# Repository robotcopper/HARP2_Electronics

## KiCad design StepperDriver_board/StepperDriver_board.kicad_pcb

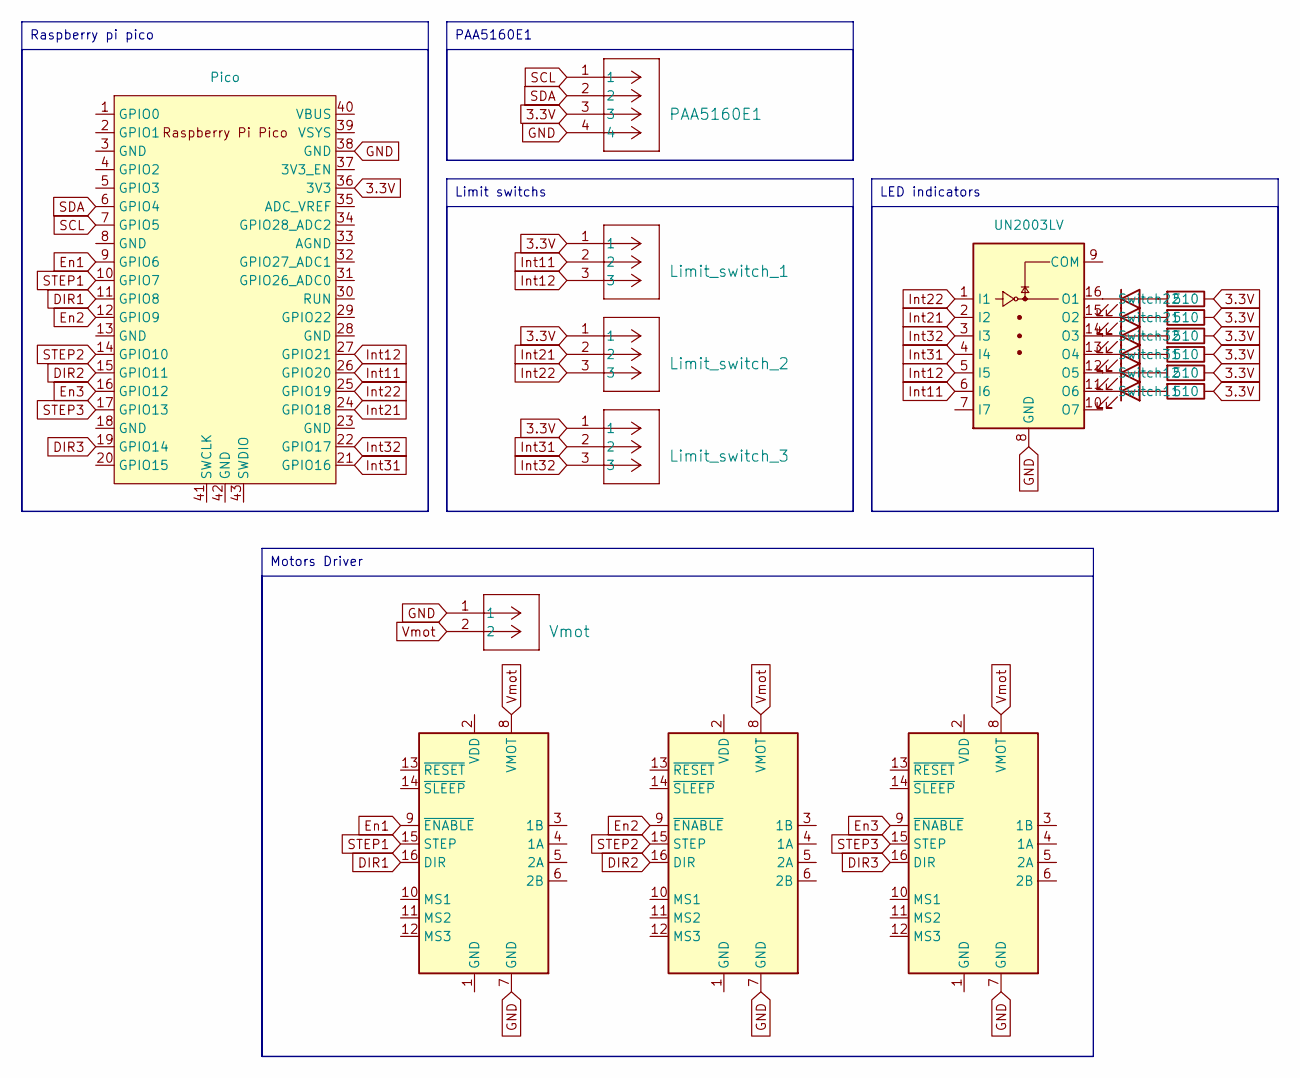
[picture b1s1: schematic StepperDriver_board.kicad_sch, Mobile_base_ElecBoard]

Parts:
A1: MKS_MotorDriver_1; Pololu_Breakout-16_15.2x20.3mm
A2: MKS_MotorDriver_2; Pololu_Breakout-16_15.2x20.3mm
A3: MKS_MotorDriver_3; Pololu_Breakout-16_15.2x20.3mm
Limit_switch_1: Limit_switch_1; CONN_B3B-PH-K-SLFSN_JST
Limit_switch_2: Limit_switch_2; CONN_B3B-PH-K-SLFSN_JST
Limit_switch_3: Limit_switch_3; CONN_B3B-PH-K-SLFSN_JST
PAA5160E1: PAA5160E1; CONN_B4B-PH-K-S_JST
R1, R2, R3, R4, R5, R6: 510; R_Axial_DIN0207_L6.3mm_D2.5mm_P7.62mm_Horizontal
Switch11: Switch11; LED_D3.0mm_Horizontal_O1.27mm_Z2.0mm
Switch12: Switch12; LED_D3.0mm_Horizontal_O1.27mm_Z2.0mm
Switch21: Switch21; LED_D3.0mm_Horizontal_O1.27mm_Z2.0mm
Switch22: Switch22; LED_D3.0mm_Horizontal_O1.27mm_Z2.0mm
Switch31: Switch31; LED_D3.0mm_Horizontal_O1.27mm_Z2.0mm
Switch32: Switch32; LED_D3.0mm_Horizontal_O1.27mm_Z2.0mm
U1: Pico; RPi_Pico_SMD_TH_2
UN2003LV1: UN2003LV; SOIC-16_3.9x9.9mm_P1.27mm
Vmot1: Vmot; CONN_B2B-XH-ALFSN_JST

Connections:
3.3V: Limit_switch_1.1, Limit_switch_2.1, Limit_switch_3.1, PAA5160E1.3, R1.1, R2.1, R3.1, R4.1, R5.1, R6.1, U1.36 (3V3)
DIR1: A1.16 (DIR), U1.11 (GPIO8)
DIR2: A2.16 (DIR), U1.15 (GPIO11)
DIR3: A3.16 (DIR), U1.19 (GPIO14)
En1: A1.9 (~ENABLE), U1.9 (GPIO6)
En2: A2.9 (~ENABLE), U1.12 (GPIO9)
En3: A3.9 (~ENABLE), U1.16 (GPIO12)
GND: A1.7 (GND), A2.7 (GND), A3.7 (GND), PAA5160E1.4, U1.38 (GND), UN2003LV1.8 (GND), Vmot1.1
Int11: Limit_switch_1.2, U1.26 (GPIO20), UN2003LV1.6 (I6)
Int12: Limit_switch_1.3, U1.27 (GPIO21), UN2003LV1.5 (I5)
Int21: Limit_switch_2.2, U1.24 (GPIO18), UN2003LV1.2 (I2)
Int22: Limit_switch_2.3, U1.25 (GPIO19), UN2003LV1.1 (I1)
Int31: Limit_switch_3.2, U1.21 (GPIO16), UN2003LV1.4 (I4)
Int32: Limit_switch_3.3, U1.22 (GPIO17), UN2003LV1.3 (I3)
unnamed: R6.2, Switch11.2 (A)
unnamed: Switch11.1 (K), UN2003LV1.11 (O6)
unnamed: R5.2, Switch12.2 (A)
unnamed: Switch12.1 (K), UN2003LV1.12 (O5)
unnamed: R2.2, Switch21.2 (A)
unnamed: Switch21.1 (K), UN2003LV1.15 (O2)
unnamed: R1.2, Switch22.2 (A)
unnamed: Switch22.1 (K), UN2003LV1.16 (O1)
unnamed: R4.2, Switch31.2 (A)
unnamed: Switch31.1 (K), UN2003LV1.13 (O4)
unnamed: R3.2, Switch32.2 (A)
unnamed: Switch32.1 (K), UN2003LV1.14 (O3)
SCL: PAA5160E1.1, U1.7 (GPIO5)
SDA: PAA5160E1.2, U1.6 (GPIO4)
STEP1: A1.15 (STEP), U1.10 (GPIO7)
STEP2: A2.15 (STEP), U1.14 (GPIO10)
STEP3: A3.15 (STEP), U1.17 (GPIO13)
Vmot: A1.8 (VMOT), A2.8 (VMOT), A3.8 (VMOT), Vmot1.2

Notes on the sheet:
Raspberry pi pico
PAA5160E1
Motors Driver
LED indicators
Limit switchs

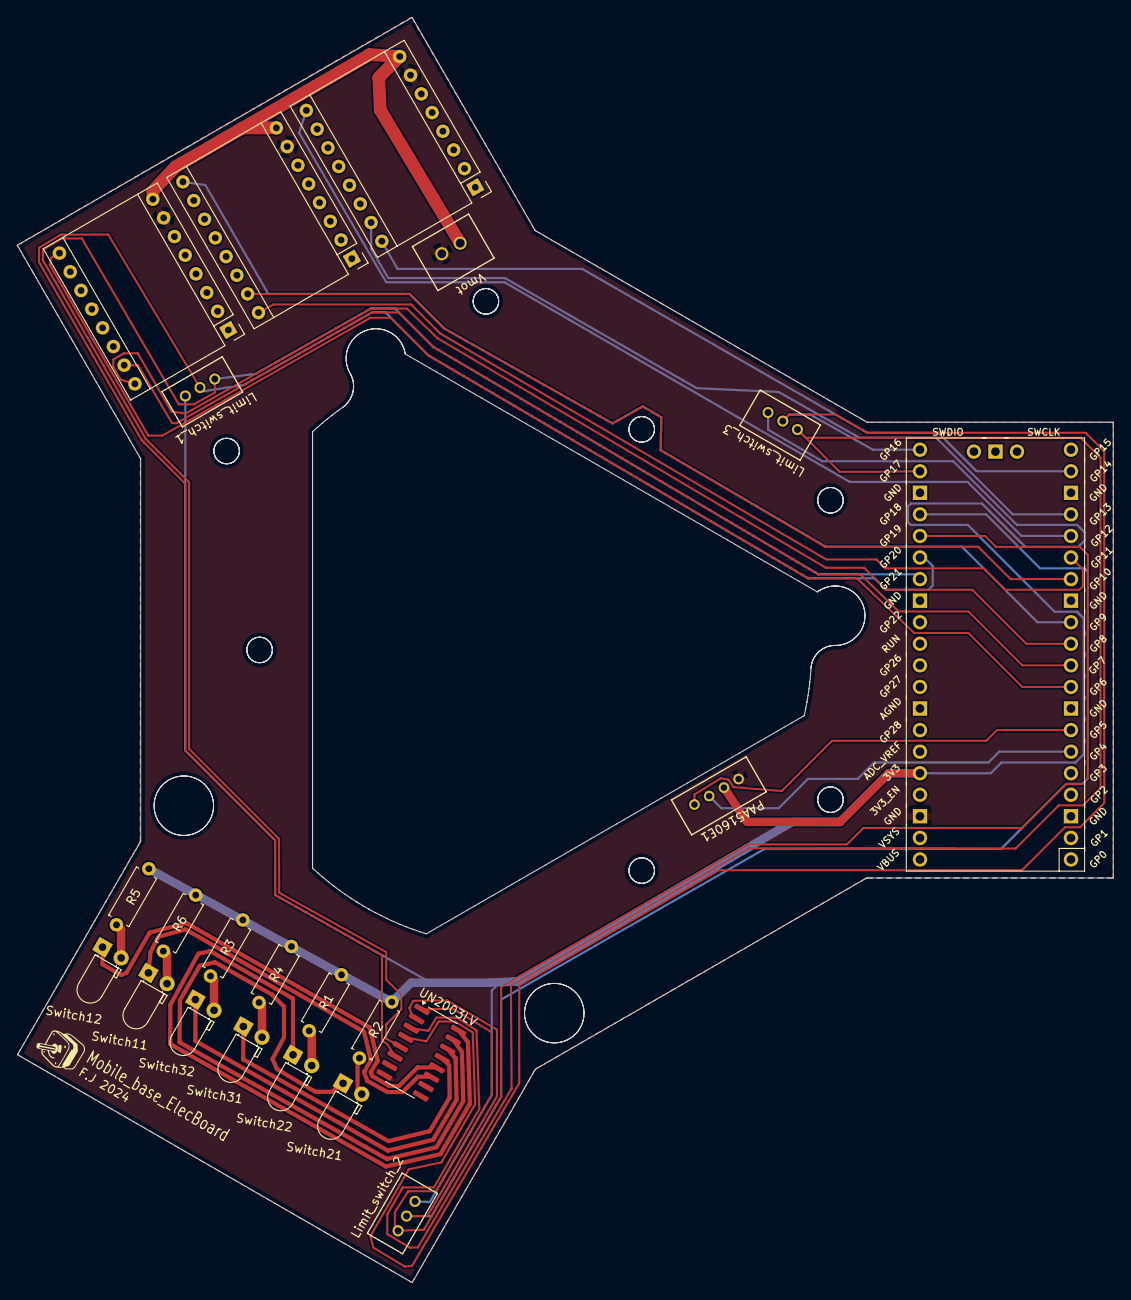
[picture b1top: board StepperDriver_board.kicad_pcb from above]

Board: 2 copper layers, 129.0 x 149.0 mm, 22 parts (0 on the bottom side), 32 nets.

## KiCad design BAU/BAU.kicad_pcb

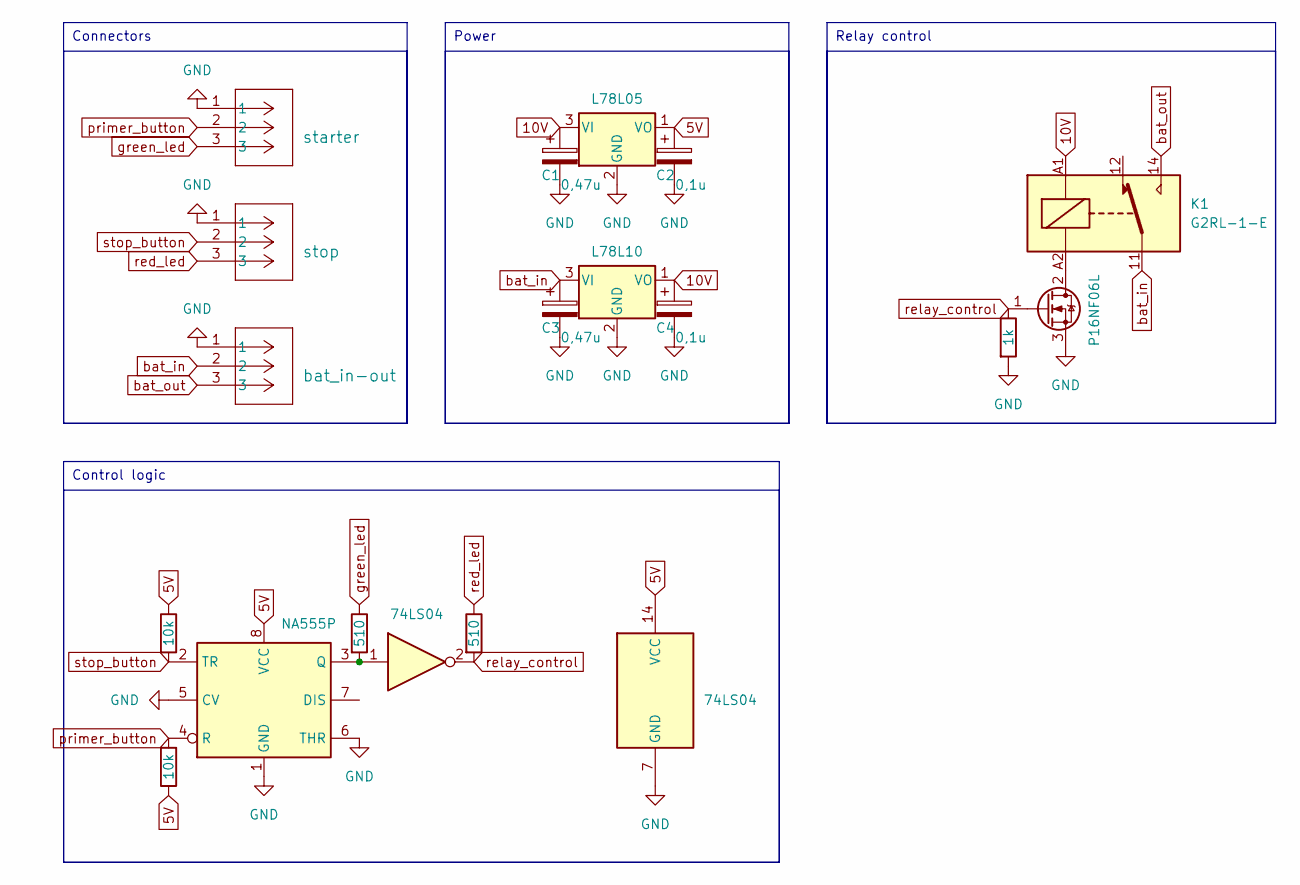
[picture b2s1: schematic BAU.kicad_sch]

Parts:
C1, C3: 0,47u; CP_Radial_D5.0mm_P2.50mm
C2, C4: 0,1u; CP_Radial_D4.0mm_P2.00mm
K1: G2RL-1-E; Relay_SPDT_Omron_G2RL-1-E
L78L05_TO92: L78L05; TO-92_Inline
L78L10_TO92: L78L10; TO-92L_Inline_Wide
NA555P1: NA555P; DIP-8_W7.62mm_Socket
P16NF06L1: P16NF06L; TO-220F-3_Vertical
R1, R2: 10k; R_Axial_DIN0207_L6.3mm_D2.5mm_P7.62mm_Horizontal
R3: 1k; R_Axial_DIN0207_L6.3mm_D2.5mm_P7.62mm_Horizontal
R4, R5: 510; R_Axial_DIN0207_L6.3mm_D2.5mm_P7.62mm_Horizontal
U2: 74LS04; DIP-14_W7.62mm_Socket
bat_in-out1: bat_in-out; CONN_S3B-XH-ALFSN_JST
starter1: starter; CONN_S3B-PH-K-S_JST
stop1: stop; CONN_S3B-PH-K-S_JST

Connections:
5V: C2.1, L78L05_TO92.1 (VO), NA555P1.8 (VCC), R1.1, R2.1, U2.14 (VCC)
10V: C1.1, C4.1, K1.A1, L78L05_TO92.3 (VI), L78L10_TO92.1 (VO)
GND: C1.2, C2.2, C3.2, C4.2, L78L05_TO92.2 (GND), L78L10_TO92.2 (GND), NA555P1.1 (GND), NA555P1.5 (CV), NA555P1.6 (THR), P16NF06L1.3 (S), R3.2, U2.7 (GND), bat_in-out1.1, starter1.1, stop1.1
unnamed: NA555P1.3 (Q), R4.2, U2.1
unnamed: K1.A2, P16NF06L1.2 (D)
bat_in: C3.1, K1.11, L78L10_TO92.3 (VI), bat_in-out1.2
bat_out: K1.14, bat_in-out1.3
green_led: R4.1, starter1.3
primer_button: NA555P1.4 (R), R2.2, starter1.2
red_led: R5.1, stop1.3
relay_control: P16NF06L1.1 (G), R3.1, R5.2, U2.2
stop_button: NA555P1.2 (TR), R1.2, stop1.2

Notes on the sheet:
Relay control
Control logic
Power
Connectors

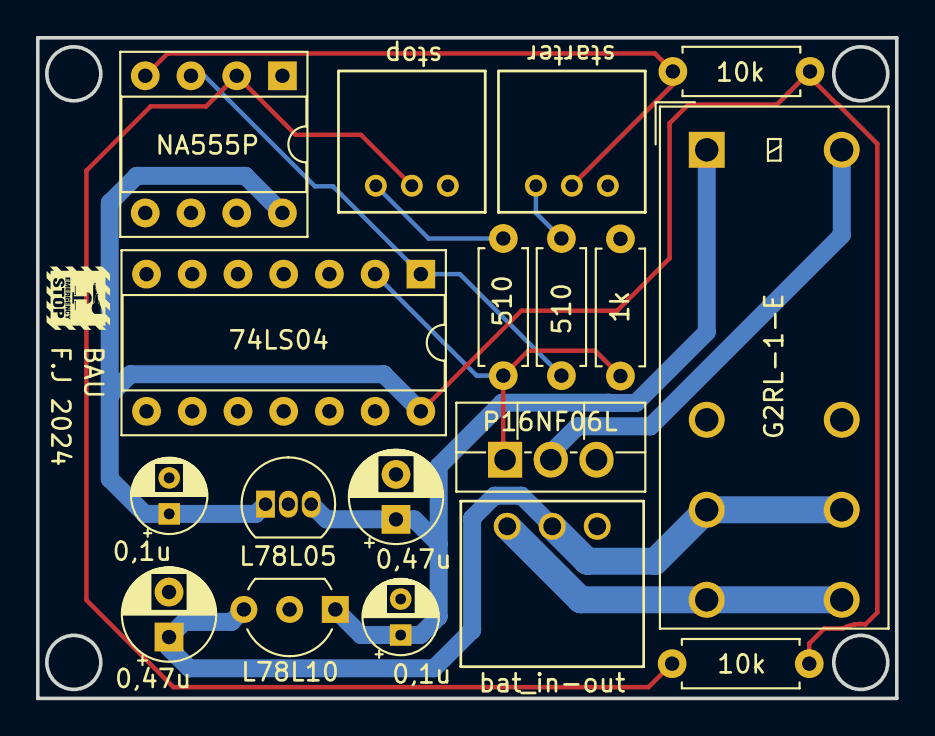
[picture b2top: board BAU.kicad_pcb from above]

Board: 2 copper layers, 47.7 x 36.7 mm, 18 parts (0 on the bottom side), 12 nets.

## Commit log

2024-08-16 Feat: MotorDriver-Elec without led indicators
2024-08-19 Feat: add LED indicators
2024-08-20 Feat: add a 7mm hole for the lidar
2024-08-21 Fix: cutted ground plan and refactor LEDs position
2024-08-26 Fix: space between LEDs
2024-09-17 Feat: add BAU elec board
2024-09-17 Feat: add gitignore
2024-10-10 Fix: missing wires
2024-10-10 Feat: add Kicad components library
2024-10-11 Feat: add XL6009 and update others
2024-10-11 Fix: update step files of stepdowns
2024-10-12 Feat: add XT60IPW-M and vertical EATON fuseholder
2024-10-12 Feat: add MKS-APT-V1.0 and RPI_Pico
2024-10-12 Feat: add JST connectors
2024-10-13 Feat: add new conectors and update footprints
2024-10-13 Feat: update footprint and add MINI560
2024-10-15 Feat: Add B2B-PH connector
2024-10-17 Feat: add B4P-VH connector
2024-10-18 Feat: add PowerBoard
2024-10-18 Chore: update .gitignore
2024-10-18 Feat: add B3PS-VH connector
2024-10-25 Feat: update PowerBoard
2024-12-04 Refactor: repos to match HARP1_Electronics refactoring
2024-12-06 Feat: add assets
